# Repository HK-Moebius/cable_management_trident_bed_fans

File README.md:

# Cable management for Trident bed fans

[Trident Bed Fans](https://github.com/VoronDesign/VoronUsers/tree/master/printer_mods/CannedBass/Trident_Bed_Fans)

[Extrusion Cover](https://github.com/VoronDesign/VoronUsers/tree/master/printer_mods/filotto78/6mm_slot_cover)

## BOM

 - 1x M3x8 SHCS
 - 1x M3 T-Nut
 - 1x Universal PCB 20mm wide 2.54mm pitch
 - 4x JST XH-2 vertical
 - 1x JST XH-2 rectangular
 - Wire 0.14mm<sup>2</sup> or e.g. twisted pair wire only for ground wiring.

### Images

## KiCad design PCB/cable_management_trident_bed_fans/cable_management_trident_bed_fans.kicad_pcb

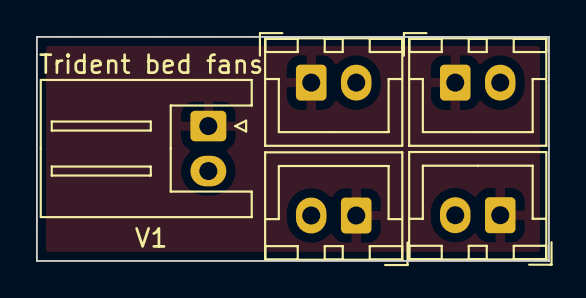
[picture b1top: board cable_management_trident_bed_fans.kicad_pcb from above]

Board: 2 copper layers, 28.4 x 12.4 mm, 5 parts (0 on the bottom side), 2 nets, no tracks yet.

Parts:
J1: Input; JST_XH_S2B-XH-A_1x02_P2.50mm_Horizontal
J2: FAN0; JST_XH_B2B-XH-A_1x02_P2.50mm_Vertical
J3: FAN1; JST_XH_B2B-XH-A_1x02_P2.50mm_Vertical
J4: FAN2; JST_XH_B2B-XH-A_1x02_P2.50mm_Vertical
J5: FAN3; JST_XH_B2B-XH-A_1x02_P2.50mm_Vertical

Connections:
/GND: J1.2, J2.2, J3.2, J4.2, J5.2
/VCC: J1.1, J2.1, J3.1, J4.1, J5.1

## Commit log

2022-05-04 Create images
2022-05-05 added KiCAD PCB
